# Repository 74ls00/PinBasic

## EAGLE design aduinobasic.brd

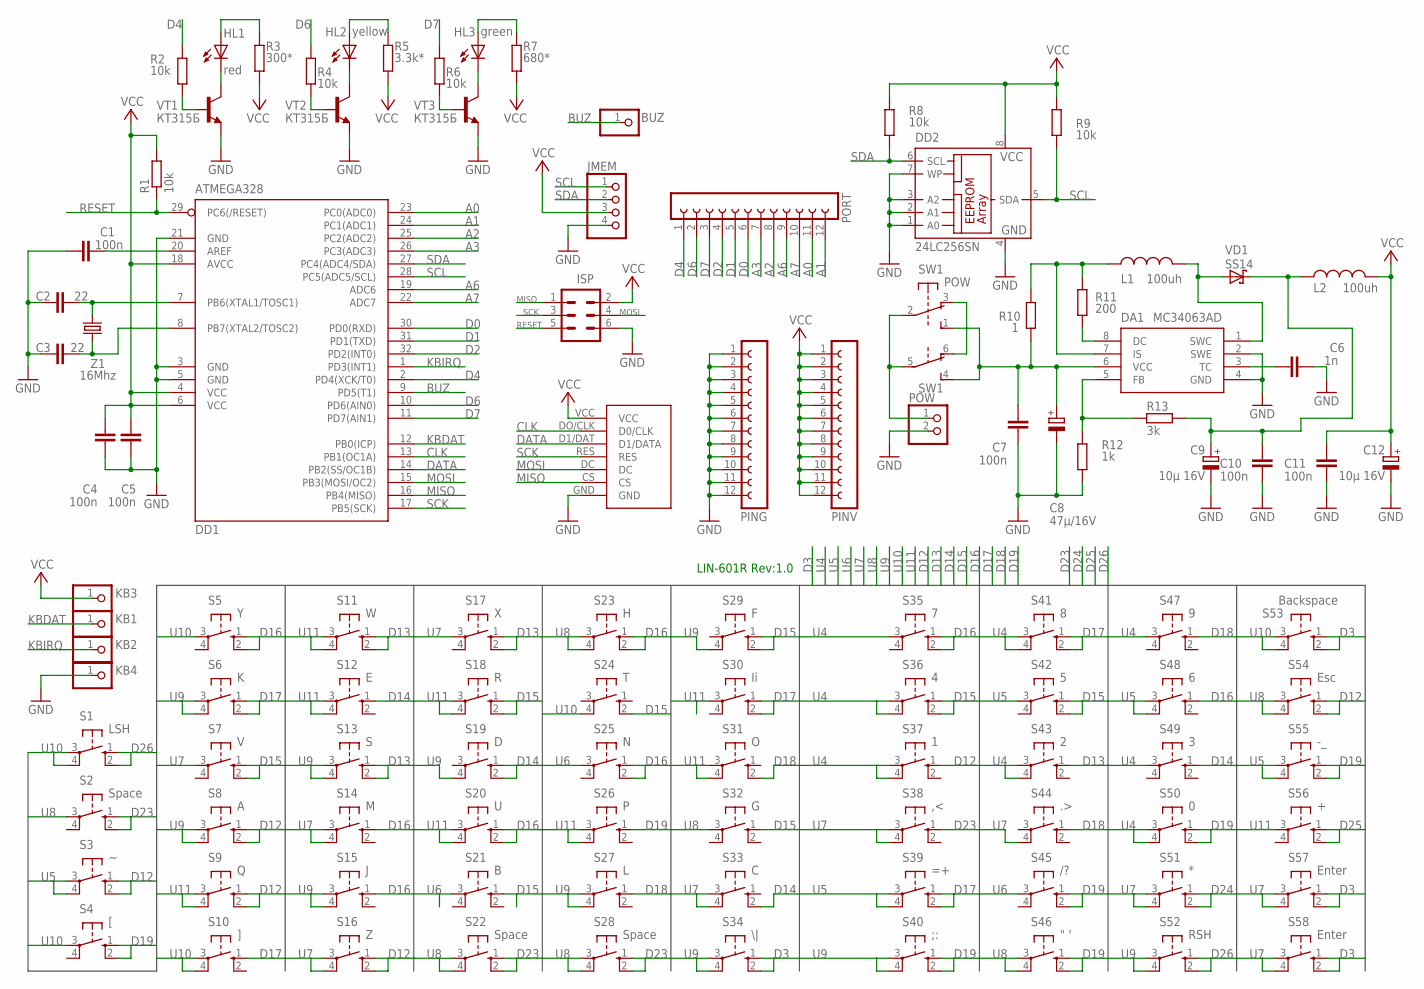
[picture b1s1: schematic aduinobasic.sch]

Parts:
BUZ: PINHD-1X1; 1X01
C1, C4, C5: 100n; C0805
C2, C3: 22; C025-025X050
C6: 1n; C025-025X050
C7, C10, C11: 100n; C1206
C8: 47µ/16V; RCL_E2-5
C9, C12: 10µ 16V; RCL_E2-5
DA1: MC34063AD; SOIC8
DD1: ATMEGA328; TQFP32-08
DD2: 24LC256SN; SO-08
DISPLAY: SSD1306; SSD1306_0.96
HL1: red; LED5MM
HL2: yellow; LED5MM
HL3: green; LED5MM
ISP: MA03-2
JMEM: PINHD-1X4; 1X04
KB1, KB2, KB3, KB4: PINHD-1X1; 1X01
L1: 100uh; 0207/10
L2: 100uh; 0204/5
PING: FE12-1; FE12
PINV: FE12-1; FE12
PORT: FE12-1; FE12
POW: PINHD-1X2; 1X02
R1, R2, R4, R6, R8, R9: 10k; R0805
R3: 300*; R1206W
R5: 3.3k*; R1206W
R7: 680*; R0805
R10: 1; M1206
R11: 200; M1206
R12: 1k; M0805
R13: 3k; M0805
S1: LSH; B3F-10XX
S2, S22, S28: Space; B3F-10XX
S3: B3F-10XX
S4: [; B3F-10XX
S5: Y; B3F-10XX
S6: K; B3F-10XX
S7: V; B3F-10XX
S8: A; B3F-10XX
S9: Q; B3F-10XX
S10: ]; B3F-10XX
S11: W; B3F-10XX
S12: E; B3F-10XX
S13: S; B3F-10XX
S14: M; B3F-10XX
S15: J; B3F-10XX
S16: Z; B3F-10XX
S17: X; B3F-10XX
S18: R; B3F-10XX
S19: D; B3F-10XX
S20: U; B3F-10XX
S21: B; B3F-10XX
S23: H; B3F-10XX
S24: T; B3F-10XX
S25: N; B3F-10XX
S26: P; B3F-10XX
S27: L; B3F-10XX
S29: F; B3F-10XX
S30: Ii; B3F-10XX
S31: O; B3F-10XX
S32: G; B3F-10XX
S33: C; B3F-10XX
S34: \|; B3F-10XX
S35: 7; B3F-10XX
S36: 4; B3F-10XX
S37: 1; B3F-10XX
S38: ,<; B3F-10XX
S39: =+; B3F-10XX
S40: ;:; B3F-10XX
S41: 8; B3F-10XX
S42: 5; B3F-10XX
S43: 2; B3F-10XX
S44: .>; B3F-10XX
S45: /?; B3F-10XX
S46: " '; B3F-10XX
S47: 9; B3F-10XX
S48: 6; B3F-10XX
S49: 3; B3F-10XX
S50: 0; B3F-10XX
S51: *; B3F-10XX
S52: RSH; B3F-10XX
S53: Backspace; B3F-10XX
S54: Esc; B3F-10XX
S55: -_; B3F-10XX
S56: +; B3F-10XX
S57, S58: Enter; B3F-10XX
SW1: POW; 9077-2
VD1: SS14; SMB
VT1, VT2, VT3: КТ315Б; TO92-ECB
Z1: 16Mhz; HC49/S

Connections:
A0: DD1.23 (PC0(ADC0)), PORT.11
A1: DD1.24 (PC1(ADC1)), PORT.12
A2: DD1.25 (PC2(ADC2)), PORT.8
A3: DD1.26 (PC3(ADC3)), PORT.7
A6: DD1.19 (ADC6), PORT.9
A7: DD1.22 (ADC7), PORT.10
AREF: C1.2, DD1.20 (AREF)
BUZ: BUZ.1, DD1.9 (PD5(T1))
CLK: DD1.13 (PB1(OC1A)), DISPLAY.DO/CLK (D0/CLK)
D0: DD1.30 (PD0(RXD)), PORT.6
D1: DD1.31 (PD1(TXD)), PORT.5
D2: DD1.32 (PD2(INT0)), PORT.4
D3: S34.1 (S), S34.2 (S1), S53.1 (S), S53.2 (S1), S57.1 (S), S57.2 (S1), S58.1 (S), S58.2 (S1)
D4: DD1.2 (PD4(XCK/T0)), PORT.1, R2.1
D6: DD1.10 (PD6(AIN0)), PORT.2, R4.1
D7: DD1.11 (PD7(AIN1)), PORT.3, R6.1
D12: S3.1 (S), S3.2 (S1), S8.1 (S), S8.2 (S1), S9.1 (S), S9.2 (S1), S16.1 (S), S16.2 (S1), S37.1 (S), S54.1 (S), S54.2 (S1)
D13: S11.1 (S), S11.2 (S1), S13.1 (S), S13.2 (S1), S17.1 (S), S17.2 (S1), S43.1 (S)
D14: S12.1 (S), S19.1 (S), S19.2 (S1), S33.2 (S1), S49.1 (S)
D15: S7.1 (S), S7.2 (S1), S18.1 (S), S18.2 (S1), S21.1 (S), S24.2 (S1), S29.1 (S), S29.2 (S1), S32.1 (S), S36.1 (S), S36.2 (S1), S42.1 (S), S42.2 (S1)
D16: S5.1 (S), S5.2 (S1), S14.1 (S), S15.1 (S), S20.1 (S), S20.2 (S1), S23.1 (S), S23.2 (S1), S25.1 (S), S25.2 (S1), S35.1 (S), S35.2 (S1), S48.1 (S)
D17: S6.1 (S), S6.2 (S1), S10.1 (S), S30.1 (S), S30.2 (S1), S39.1 (S), S39.2 (S1), S41.1 (S), S41.2 (S1)
D18: S27.1 (S), S31.2 (S1), S44.1 (S), S47.1 (S)
D19: S4.1 (S), S4.2 (S1), S26.1 (S), S40.1 (S), S40.2 (S1), S45.1 (S), S45.2 (S1), S46.1 (S), S46.2 (S1), S50.1 (S), S50.2 (S1), S55.1 (S), S55.2 (S1)
D23: S2.1 (S), S2.2 (S1), S22.1 (S), S22.2 (S1), S28.1 (S), S28.2 (S1), S38.1 (S)
D24: S51.1 (S), S51.2 (S1)
D25: S56.1 (S), S56.2 (S1)
D26: S1.1 (S), S1.2 (S1), S52.1 (S), S52.2 (S1)
DATA: DD1.14 (PB2(SS/OC1B)), DISPLAY.D1/DAT (D1/DATA)
GND: C1.1, C2.1, C3.1, C4.2, C5.2, C6.2, C7.2, C8.-, C9.-, C10.1, C11.1, C12.-, DA1.2 (SWE), DA1.4 (GND), DD1.3 (GND), DD1.5 (GND), DD1.21 (GND), DD2.1 (A0), DD2.2 (A1), DD2.3 (A2), DD2.4 (GND), DD2.7 (WP), DISPLAY.GND, ISP.6, JMEM.4, KB4.1, PING.1, PING.2, PING.3, PING.4, PING.5, PING.6, PING.7, PING.8, PING.9, PING.10, PING.11, PING.12, POW.2, R12.1, VT1.E, VT2.E, VT3.E
KBDAT: DD1.12 (PB0(ICP)), KB1.1
KBIRQ: DD1.1 (PD3(INT1)), KB2.1
MISO: DD1.16 (PB4(MISO)), DISPLAY.CS, ISP.1
MOSI: DD1.15 (PB3(MOSI/OC2)), DISPLAY.DC, ISP.4
unnamed: C2.2, DD1.7 (PB6(XTAL1/TOSC1)), Z1.2
unnamed: C3.2, DD1.8 (PB7(XTAL2/TOSC2)), Z1.1
unnamed: C7.1, C8.+, DA1.6 (VCC), R10.1, SW1.1 (S), SW1.4 (S)
unnamed: POW.1, SW1.2, SW1.5
unnamed: DA1.8 (DC), R11.1
unnamed: DA1.7 (IS), L1.1, R10.2, R11.2
unnamed: DA1.5 (FB), R12.2, R13.1
unnamed: DA1.1 (SWC), L1.2, VD1.A
unnamed: C6.1, DA1.3 (TC)
unnamed: SW1.3 (O), SW1.6 (O)
unnamed: HL1.K (C), VT1.C
unnamed: R2.2, VT1.B
unnamed: HL1.A, R3.1
unnamed: HL2.K (C), VT2.C
unnamed: R4.2, VT2.B
unnamed: HL2.A, R5.1
unnamed: HL3.K (C), VT3.C
unnamed: R6.2, VT3.B
unnamed: HL3.A, R7.1
unnamed: C9.+, C10.2, L2.1, R13.2, VD1.C
RESET: DD1.29 (PC6(/RESET)), ISP.5, R1.1
SCK: DD1.17 (PB5(SCK)), DISPLAY.RES, ISP.3
SCL: DD1.28 (PC5(ADC5/SCL)), DD2.5 (SDA), JMEM.1, R9.1
SDA: DD1.27 (PC4(ADC4/SDA)), DD2.6 (SCL), JMEM.2, R8.1
U4: S35.3, S36.3, S36.4 (P1), S37.3, S37.4 (P1), S41.3, S41.4 (P1), S43.3, S43.4 (P1), S47.3, S49.3, S50.3, S50.4 (P1)
U5: S3.3, S3.4 (P1), S39.3, S39.4 (P1), S42.3, S48.3, S48.4 (P1), S55.3, S55.4 (P1)
U6: S21.3, S25.3, S45.3
U7: S7.3, S14.3, S14.4 (P1), S16.3, S16.4 (P1), S17.3, S33.3, S33.4 (P1), S38.3, S38.4 (P1), S44.4 (P1), S51.3, S51.4 (P1), S57.3, S57.4 (P1), S58.3, S58.4 (P1)
U8: S2.3, S22.3, S22.4 (P1), S23.3, S23.4 (P1), S28.3, S28.4 (P1), S32.3, S46.3, S46.4 (P1), S54.3, S54.4 (P1)
U9: S6.3, S6.4 (P1), S8.3, S8.4 (P1), S13.3, S13.4 (P1), S15.3, S15.4 (P1), S19.4 (P1), S27.3, S27.4 (P1), S29.4 (P1), S34.3, S34.4 (P1), S40.3, S40.4 (P1), S52.3, S52.4 (P1)
U10: S1.3, S1.4 (P1), S4.3, S5.3, S10.3, S10.4 (P1), S24.4 (P1), S53.3, S53.4 (P1)
U11: S9.3, S9.4 (P1), S11.3, S11.4 (P1), S12.3, S12.4 (P1), S18.3, S18.4 (P1), S20.3, S20.4 (P1), S26.3, S26.4 (P1), S30.3, S31.3, S31.4 (P1), S56.3
VCC: C4.1, C5.1, C11.2, C12.+, DD1.4 (VCC), DD1.6 (VCC), DD1.18 (AVCC), DD2.8 (VCC), DISPLAY.VCC, ISP.2, JMEM.3, KB3.1, L2.2, PINV.1, PINV.2, PINV.3, PINV.4, PINV.5, PINV.6, PINV.7, PINV.8, PINV.9, PINV.10, PINV.11, PINV.12, R1.2, R3.2, R5.2, R7.2, R8.2, R9.2

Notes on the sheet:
LIN-601R Rev:1.0

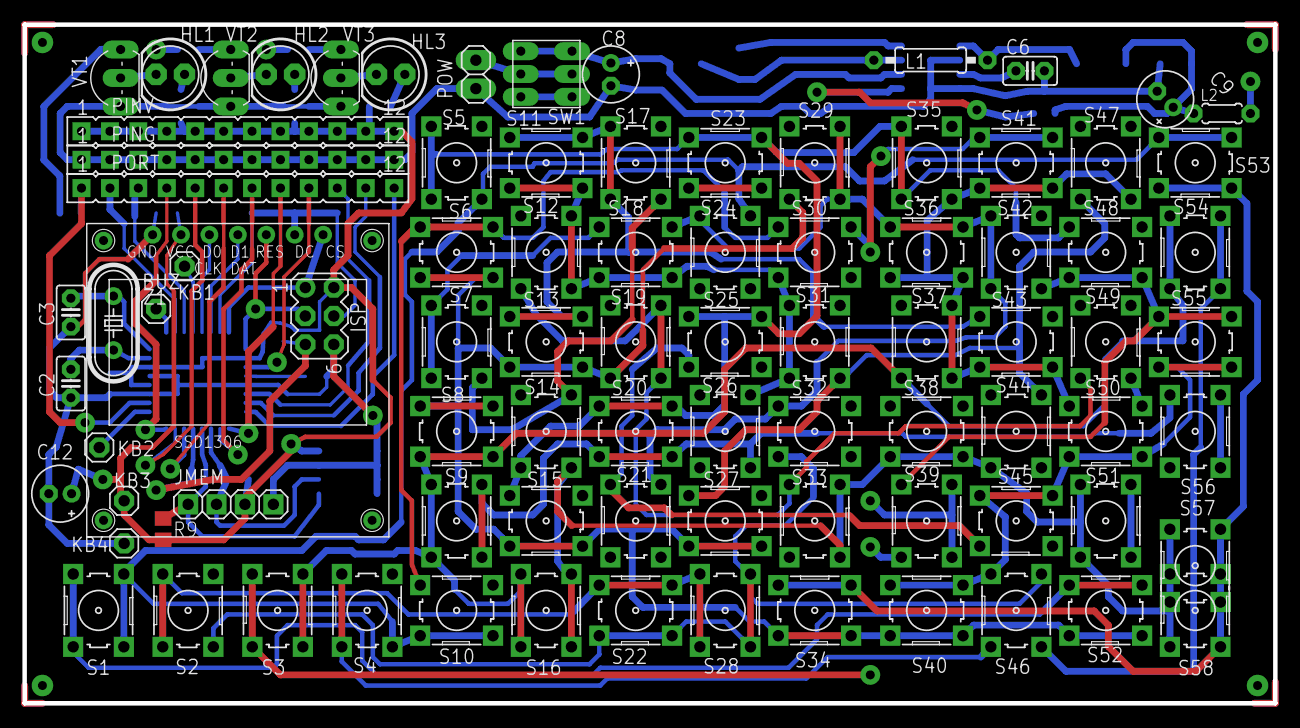
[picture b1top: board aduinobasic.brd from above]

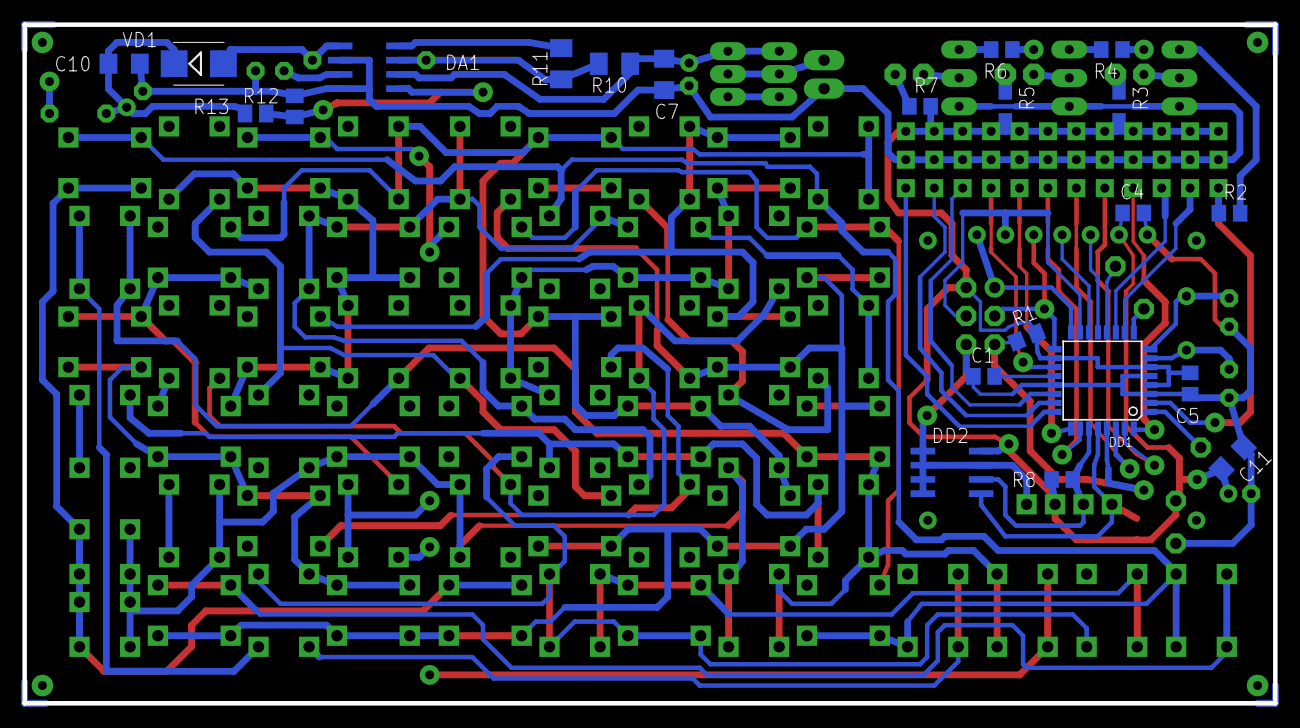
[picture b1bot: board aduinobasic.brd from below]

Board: 2 copper layers, 111.8 x 60.6 mm, 109 parts (22 on the bottom side), 67 nets.
